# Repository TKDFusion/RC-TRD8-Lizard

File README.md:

Lizard is a 3D printed RC race car for onroad usage. The full description of this project is available on Instructables: https://www.instructables.com/Lizard-3D-Printed-RC-Race-Car/

Here, you can find the Gerber files for the PCBs and the sketches required for the ESP32 microcontroller in the remote control and in the car. Also, you can find the codes required to operate a separate data logger alongside the car, including MATLAB functions to evaluate the recorded data graphically. Further, all files for printing are provided as .stl and .stp files.

Also, I added the BOM as an Excel file, and you can find .stp files of the different part groups as well as of the full car assembly, as an aid in assembling the car.

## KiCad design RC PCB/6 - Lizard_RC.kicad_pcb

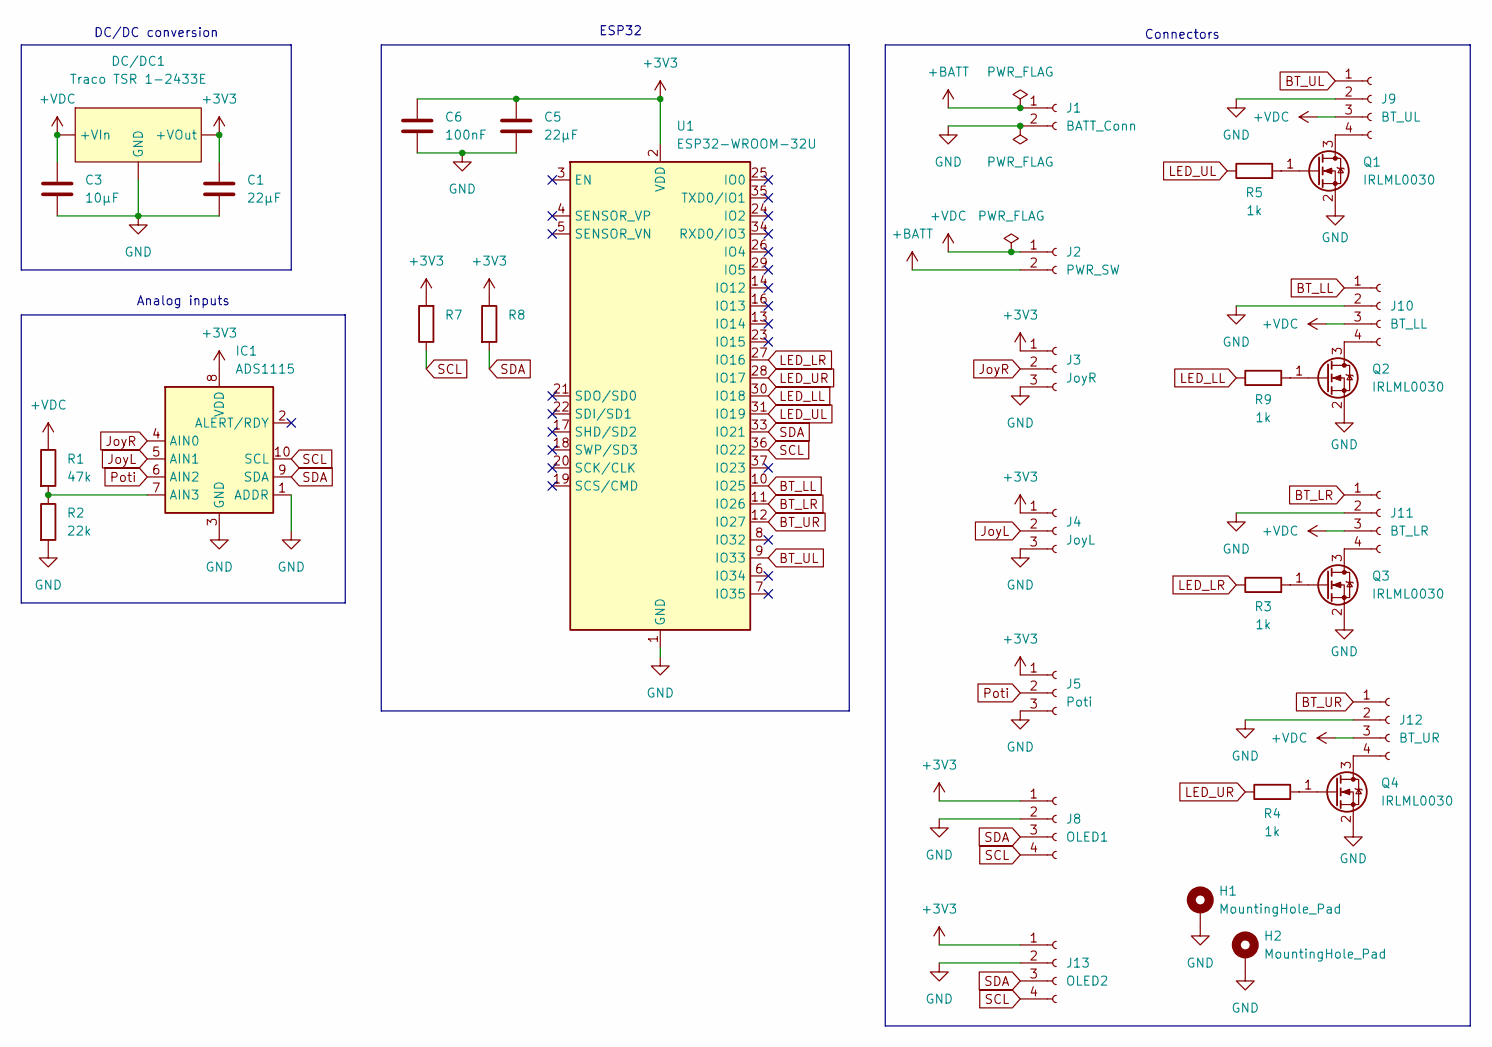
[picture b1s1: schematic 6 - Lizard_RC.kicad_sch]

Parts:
C1, C5: 22µF; C_1206_3216Metric_Pad1.33x1.80mm_HandSolder
C3: 10µF; C_2220_5750Metric_Pad1.97x5.40mm_HandSolder
C6: 100nF; C_0805_2012Metric_Pad1.18x1.45mm_HandSolder
DC/DC1: Traco TSR 1-2433E; LME78_03-1.0
H1, H2: MountingHole_Pad; MountingHole_3.5mm_Pad_TopBottom
IC1: ADS1115
J1: BATT_Conn; Molex_SL_171971-0002_1x02_P2.54mm_Vertical
J2: PWR_SW; Molex_SL_171971-0002_1x02_P2.54mm_Vertical
J3: JoyR; Molex_SL_171971-0003_1x03_P2.54mm_Vertical
J4: JoyL; Molex_SL_171971-0003_1x03_P2.54mm_Vertical
J5: Poti; Molex_SL_171971-0003_1x03_P2.54mm_Vertical
J8: OLED1; Molex_SL_171971-0004_1x04_P2.54mm_Vertical
J9: BT_UL; Molex_SL_171971-0004_1x04_P2.54mm_Vertical
J10: BT_LL; Molex_SL_171971-0004_1x04_P2.54mm_Vertical
J11: BT_LR; Molex_SL_171971-0004_1x04_P2.54mm_Vertical
J12: BT_UR; Molex_SL_171971-0004_1x04_P2.54mm_Vertical
J13: OLED2; Molex_SL_171971-0004_1x04_P2.54mm_Vertical
Q1, Q2, Q3, Q4: IRLML0030; SOT-23_Handsoldering
R1: 47k; R_Axial_DIN0309_L9.0mm_D3.2mm_P12.70mm_Horizontal
R2: 22k; R_Axial_DIN0309_L9.0mm_D3.2mm_P12.70mm_Horizontal
R3, R4, R5, R9: 1k; R_Axial_DIN0309_L9.0mm_D3.2mm_P12.70mm_Horizontal
R7, R8: R_Axial_DIN0309_L9.0mm_D3.2mm_P12.70mm_Horizontal
U1: ESP32-WROOM-32U; NodeMCU-ESP32

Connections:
+3V3: C1.1, C5.1, C6.1, DC/DC1.3 (+VOut), IC1.8 (VDD), J3.1, J4.1, J5.1, J8.1, J13.1, R7.2, R8.1, U1.2 (VDD)
+BATT: J1.1, J2.2
+VDC: C3.1, DC/DC1.1 (+VIn), J2.1, J9.3, J10.3, J11.3, J12.3, R1.1
BT_LL: J10.1, U1.10 (IO25)
BT_LR: J11.1, U1.11 (IO26)
BT_UL: J9.1, U1.9 (IO33)
BT_UR: J12.1, U1.12 (IO27)
GND: C1.2, C3.2, C5.2, C6.2, DC/DC1.2 (GND), H1.1, H2.1, IC1.1 (ADDR), IC1.3 (GND), J1.2, J3.3, J4.3, J5.3, J8.2, J9.2, J10.2, J11.2, J12.2, J13.2, Q1.2 (S), Q2.2 (S), Q3.2 (S), Q4.2 (S), R2.2, U1.1 (GND), U1.15 (GND), U1.38 (GND)
JoyL: IC1.5 (AIN1), J4.2
JoyR: IC1.4 (AIN0), J3.2
LED_LL: R9.1, U1.30 (IO18)
LED_LR: R3.1, U1.27 (IO16)
LED_UL: R5.1, U1.31 (IO19)
LED_UR: R4.1, U1.28 (IO17)
unnamed: IC1.7 (AIN3), R1.2, R2.1
unnamed: J9.4, Q1.3 (D)
unnamed: J10.4, Q2.3 (D)
unnamed: J11.4, Q3.3 (D)
unnamed: J12.4, Q4.3 (D)
unnamed: Q1.1 (G), R5.2
unnamed: Q2.1 (G), R9.2
unnamed: Q3.1 (G), R3.2
unnamed: Q4.1 (G), R4.2
Poti: IC1.6 (AIN2), J5.2
SCL: IC1.10 (SCL), J8.4, J13.4, R7.1, U1.36 (IO22)
SDA: IC1.9 (SDA), J8.3, J13.3, R8.2, U1.33 (IO21)

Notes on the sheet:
DC/DC conversion
ESP32
Connectors
Analog inputs

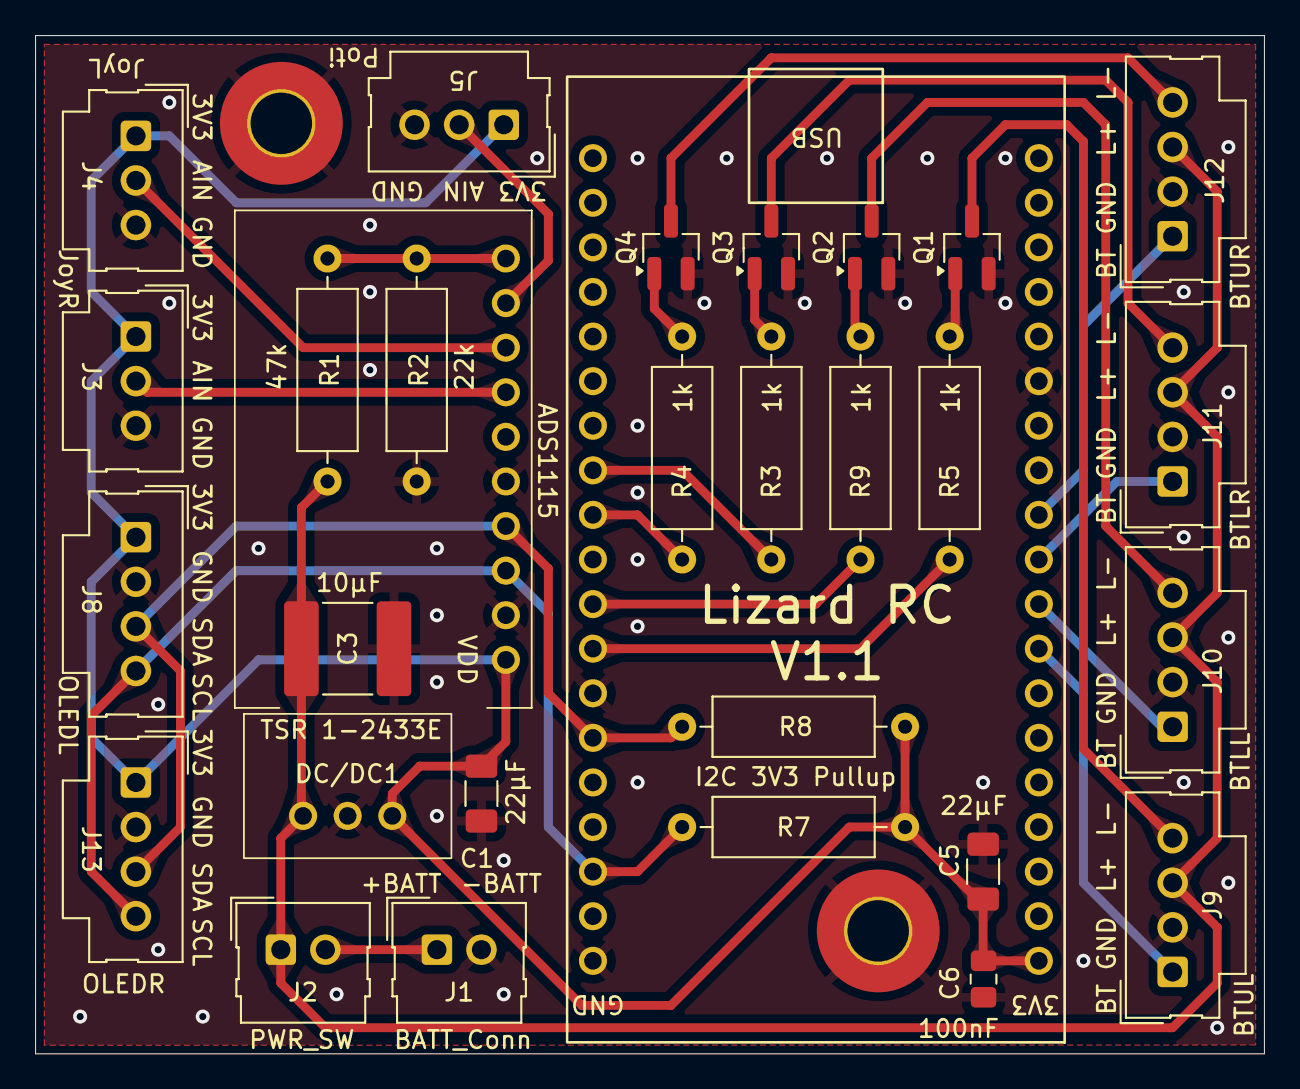
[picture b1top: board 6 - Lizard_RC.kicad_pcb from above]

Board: 2 copper layers, 70.0 x 58.0 mm, 32 parts (0 on the bottom side), 26 nets.

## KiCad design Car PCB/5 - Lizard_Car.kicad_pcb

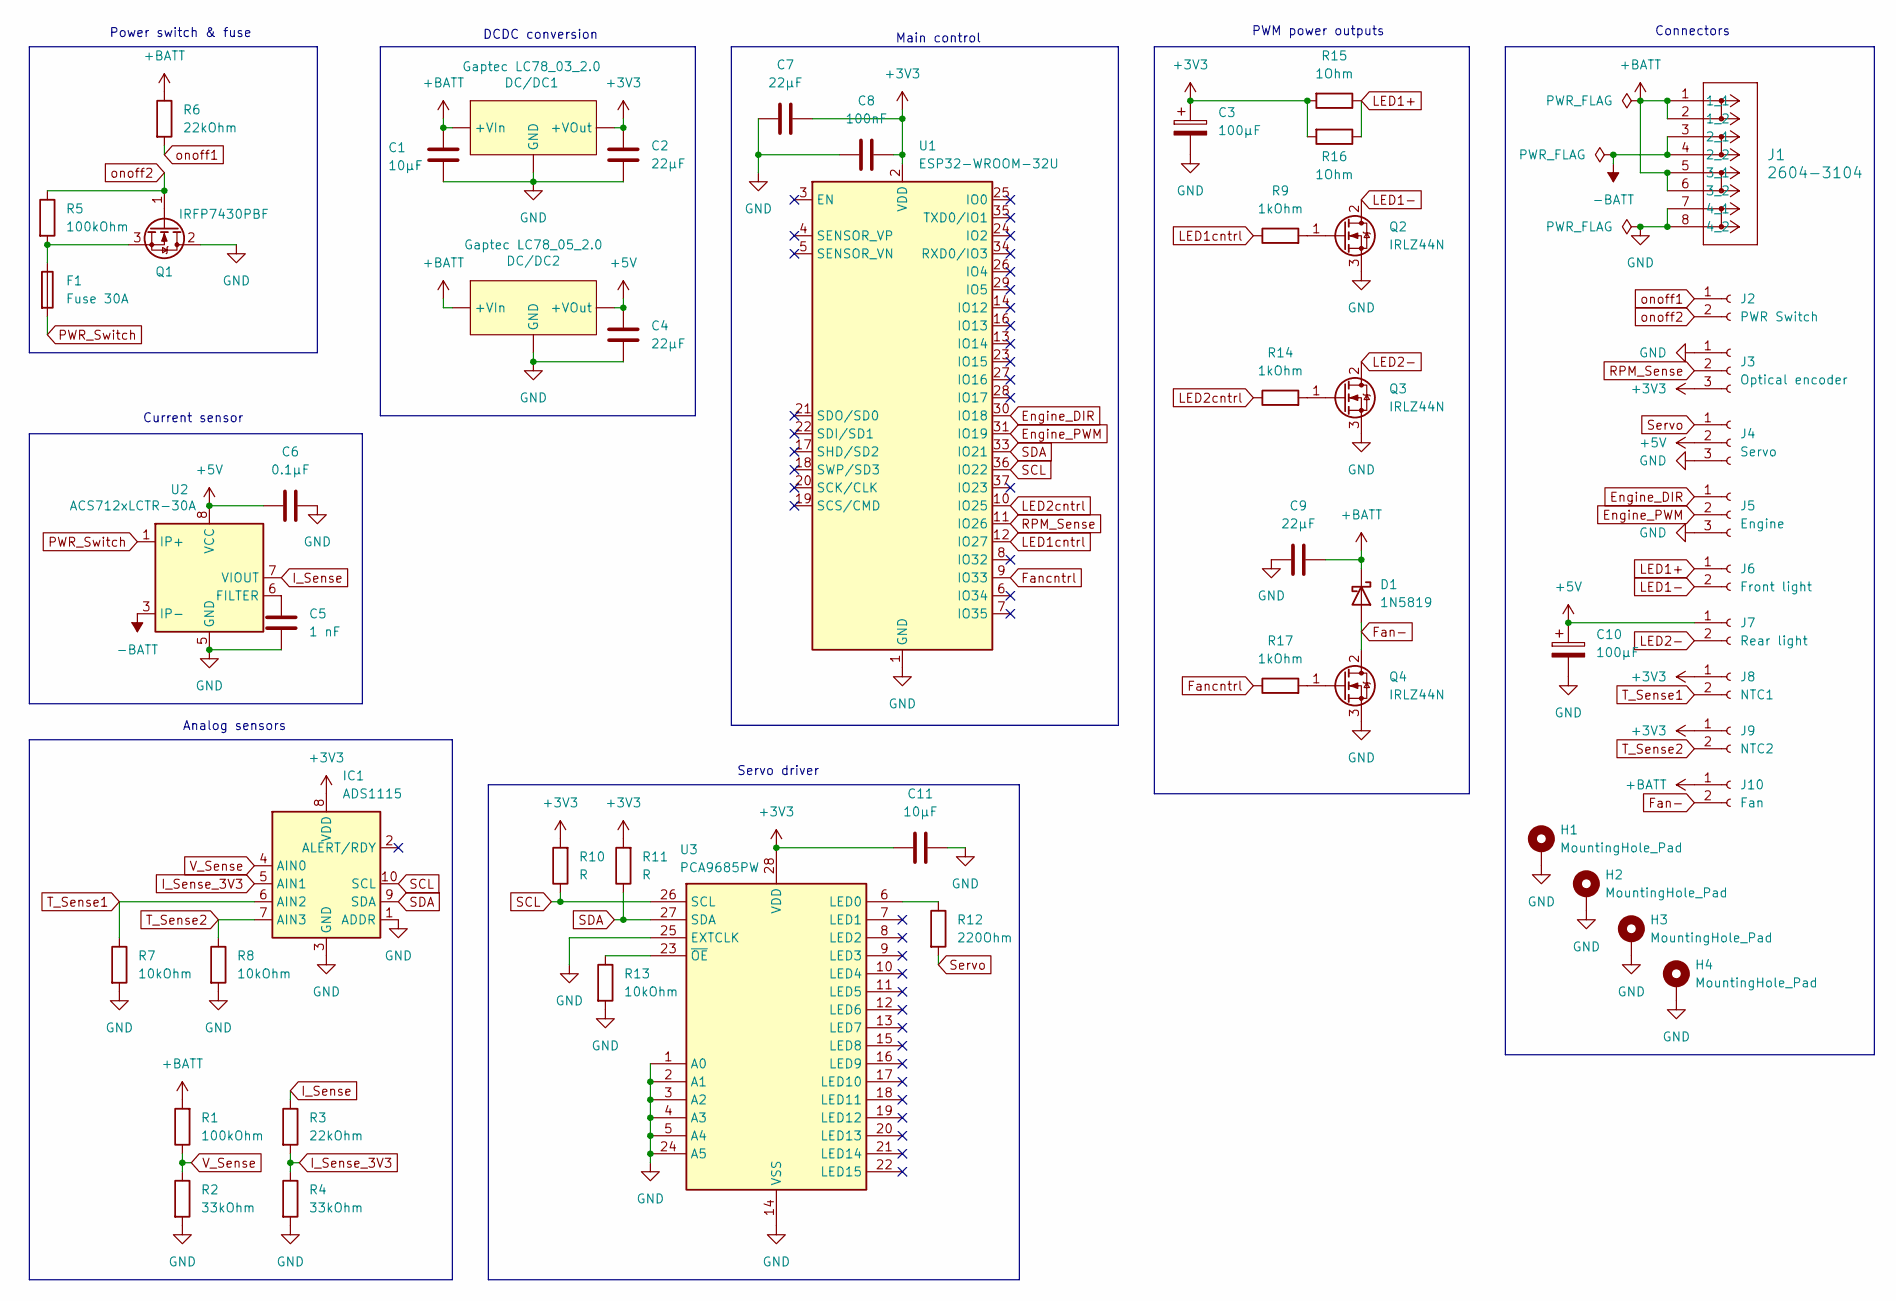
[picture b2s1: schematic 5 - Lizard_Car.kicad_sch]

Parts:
C1: 10µF; C_2220_5750Metric_Pad1.97x5.40mm_HandSolder
C2, C4, C7, C9: 22µF; C_1206_3216Metric_Pad1.33x1.80mm_HandSolder
C3, C10: 100µF; CP_Radial_D10.0mm_P5.00mm
C5: 1 nF; C_0805_2012Metric_Pad1.18x1.45mm_HandSolder
C6: 0.1µF; C_0805_2012Metric_Pad1.18x1.45mm_HandSolder
C8: 100nF; C_0805_2012Metric_Pad1.18x1.45mm_HandSolder
C11: 10µF; C_0805_2012Metric_Pad1.18x1.45mm_HandSolder
D1: 1N5819; D_DO-41_SOD81_P10.16mm_Horizontal
DC/DC1: Gaptec LC78_03_2.0; LC78_05_2.0
DC/DC2: Gaptec LC78_05_2.0; LC78_05_2.0
F1: Fuse 30A; iMAXX_H7810
H1, H2, H3, H4: MountingHole_Pad; MountingHole_3.2mm_M3_Pad_TopBottom
IC1: ADS1115
J1: 2604-3104; CONN4_2604-3104_WAG
J2: PWR Switch; Molex_SL_171971-0002_1x02_P2.54mm_Vertical
J3: Optical encoder; Molex_SL_171971-0003_1x03_P2.54mm_Vertical
J4: Servo; Molex_SL_171971-0003_1x03_P2.54mm_Vertical
J5: Engine; Molex_SL_171971-0003_1x03_P2.54mm_Vertical
J6: Front light; Molex_SL_171971-0002_1x02_P2.54mm_Vertical
J7: Rear light; Molex_SL_171971-0002_1x02_P2.54mm_Vertical
J8: NTC1; Molex_SL_171971-0002_1x02_P2.54mm_Vertical
J9: NTC2; Molex_SL_171971-0002_1x02_P2.54mm_Vertical
J10: Fan; Molex_SL_171971-0002_1x02_P2.54mm_Vertical
Q1: IRFP7430PBF; TO247 vertical MOSFET
Q2, Q3, Q4: IRLZ44N; TO-220-3_Vertical
R1, R5: 100kOhm; R_Axial_DIN0309_L9.0mm_D3.2mm_P2.54mm_Vertical
R2, R4: 33kOhm; R_Axial_DIN0309_L9.0mm_D3.2mm_P2.54mm_Vertical
R3, R6: 22kOhm; R_Axial_DIN0309_L9.0mm_D3.2mm_P2.54mm_Vertical
R7, R8: 10kOhm; R_Axial_DIN0309_L9.0mm_D3.2mm_P12.70mm_Horizontal
R9, R14, R17: 1kOhm; R_Axial_DIN0309_L9.0mm_D3.2mm_P2.54mm_Vertical
R10, R11: R; R_Axial_DIN0309_L9.0mm_D3.2mm_P2.54mm_Vertical
R12: 220Ohm; R_Axial_DIN0309_L9.0mm_D3.2mm_P12.70mm_Horizontal
R13: 10kOhm; R_Axial_DIN0309_L9.0mm_D3.2mm_P2.54mm_Vertical
R15, R16: 1Ohm; R_Axial_DIN0309_L9.0mm_D3.2mm_P2.54mm_Vertical
U1: ESP32-WROOM-32U; NodeMCU-ESP32
U2: ACS712xLCTR-30A; SOIC-8_3.9x4.9mm_P1.27mm
U3: PCA9685PW; TSSOP-28_4.4x9.7mm_P0.65mm

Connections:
+3V3: C2.1, C3.1, C7.1, C8.1, C11.1, DC/DC1.3 (+VOut), IC1.8 (VDD), J3.3, J8.1, J9.1, R10.2, R11.2, R15.2, R16.2, U1.2 (VDD), U3.28 (VDD)
+5V: C4.1, C6.2, C10.1, DC/DC2.3 (+VOut), J4.2, J7.1, U2.8 (VCC)
+BATT: C1.1, C9.1, D1.1 (K), DC/DC1.1 (+VIn), DC/DC2.1 (+VIn), J1.1 (1_1), J1.2 (1_2), J1.5 (3_1), J1.6 (3_2), J10.1, R1.2, R6.1
-BATT: J1.3 (2_1), J1.4 (2_2), U2.3 (IP-), U2.4 (IP-)
Engine_DIR: J5.1, U1.30 (IO18)
Engine_PWM: J5.2, U1.31 (IO19)
Fan-: D1.2 (A), J10.2, Q4.2 (D)
Fancntrl: R17.1, U1.9 (IO33)
GND: C1.2, C2.2, C3.2, C4.2, C5.2, C6.1, C7.2, C8.2, C9.2, C10.2, C11.2, DC/DC1.2 (GND), DC/DC2.2 (GND), H1.1, H2.1, H3.1, H4.1, IC1.1 (ADDR), IC1.3 (GND), J1.7 (4_1), J1.8 (4_2), J3.1, J4.3, J5.3, Q1.2 (D), Q2.3 (S), Q3.3 (S), Q4.3 (S), R2.2, R4.2, R7.2, R8.2, R13.2, U1.1 (GND), U1.15 (GND), U1.38 (GND), U2.5 (GND), U3.1 (A0), U3.2 (A1), U3.3 (A2), U3.4 (A3), U3.5 (A4), U3.14 (VSS), U3.24 (A5), U3.25 (EXTCLK)
I_Sense: R3.1, U2.7 (VIOUT)
I_Sense_3V3: IC1.5 (AIN1), R3.2, R4.1
LED1+: J6.1, R15.1, R16.1
LED1-: J6.2, Q2.2 (D)
LED1cntrl: R9.1, U1.12 (IO27)
LED2-: J7.2, Q3.2 (D)
LED2cntrl: R14.1, U1.10 (IO25)
unnamed: F1.1, Q1.3 (S), R5.2
unnamed: Q2.1 (G), R9.2
unnamed: Q3.1 (G), R14.2
unnamed: Q4.1 (G), R17.2
unnamed: C5.1, U2.6 (FILTER)
unnamed: R12.1, U3.6 (LED0)
unnamed: R13.1, U3.23 (~OE)
PWR_Switch: F1.2, U2.1 (IP+), U2.2 (IP+)
RPM_Sense: J3.2, U1.11 (IO26)
SCL: IC1.10 (SCL), R10.1, U1.36 (IO22), U3.26 (SCL)
SDA: IC1.9 (SDA), R11.1, U1.33 (IO21), U3.27 (SDA)
Servo: J4.1, R12.2
T_Sense1: IC1.6 (AIN2), J8.2, R7.1
T_Sense2: IC1.7 (AIN3), J9.2, R8.1
V_Sense: IC1.4 (AIN0), R1.1, R2.1
onoff1: J2.1, R6.2
onoff2: J2.2, Q1.1 (G), R5.1

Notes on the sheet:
Current sensor
Connectors
PWM power outputs
Servo driver
Analog sensors
DCDC conversion
Power switch & fuse
Main control

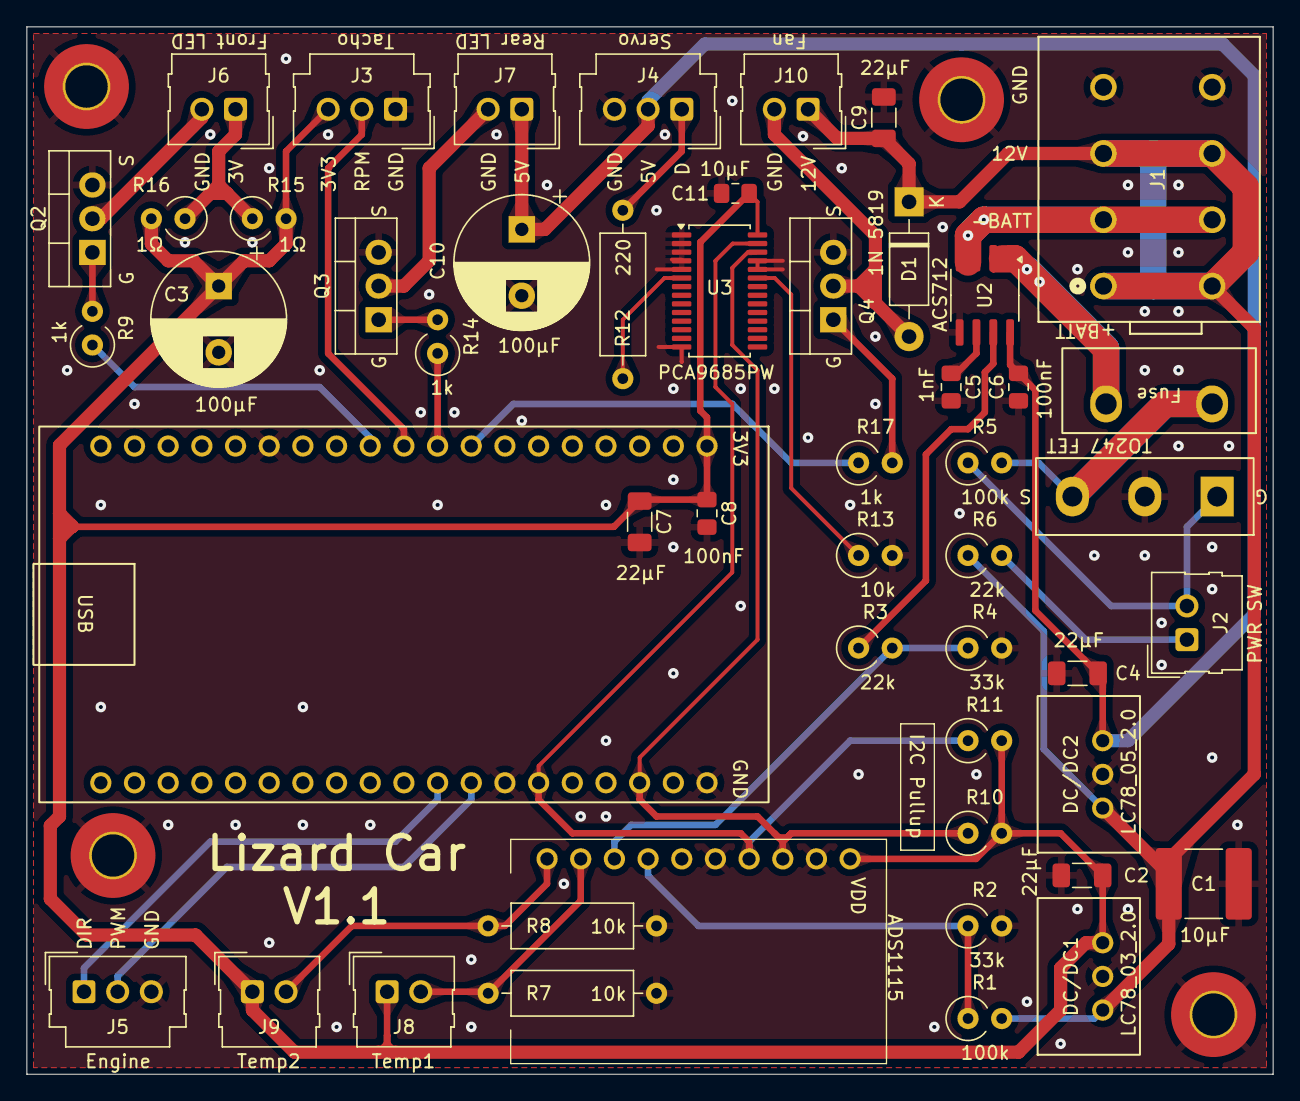
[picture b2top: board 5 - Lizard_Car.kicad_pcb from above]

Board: 2 copper layers, 94.0 x 79.0 mm, 54 parts (0 on the bottom side), 33 nets.

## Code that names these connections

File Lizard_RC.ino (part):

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#include <Preferences.h> //library for storing variables in flash memory

//Pin definitions
#define LED_LR 16
#define LED_UR 17
#define LED_LL 18
#define LED_UL 19
#define BTN_LR 26
#define BTN_LL 25
#define BTN_UR 27
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//Add I2C peripherals
//ADS1115
Adafruit_ADS1115 adc; //ADC
int joyr = 0; //these variables indicate the input channel population of the ADC (right and left joystick, poti)
int joyl = 1;
int poti = 2;
int batt = 3;

//2x SSD1306 OLED display
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    outgoing.rearlight=rlightint;
  }

  pinMode(LED_LR, OUTPUT);
  pinMode(LED_UR, OUTPUT);
  pinMode(LED_UL, OUTPUT);
  pinMode(LED_LL, OUTPUT);
  digitalWrite(LED_LR, LOW);
  digitalWrite(LED_UR, LOW);
  digitalWrite(LED_UL, LOW);
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
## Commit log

2025-05-09 Create Lizard_Logger
2025-05-09 Create Lizard_Car
2025-05-10 Create Stepfiles
2025-05-10 Create STL
2025-05-10 Create abc
2025-08-14 Rename Lizard_Logger to Lizard_Logger.ino
2025-08-14 Rename Lizard_Car to Lizard_Car.ino
